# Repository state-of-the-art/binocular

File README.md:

# Binocular

Project aims to design the open hardware binocular wearing computer platform. It's PCB design and
the related software should be open to drive the development of VR/AR glasses for masses.

## Project Goal

To speedup the future come, where AR is a necessary part of the regular reality, like internet now.

## Designs

* [Prototype 1](design/prototype_1)

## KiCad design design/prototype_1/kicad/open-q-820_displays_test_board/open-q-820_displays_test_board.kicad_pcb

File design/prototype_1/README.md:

# Prototype 1

The first prototype with the custom PCB design to fuse the SOM and modules together. Basically it
contains a number of buttons, leds, dual USB-C interface and a way to put SOM in place and connect
the displays.

## Requirements

1. Open Source and Open Hardware platform for light-weight wearable stereo displays as close as
currently possible to the regular glasses
2. No AR-grade positioning detection - just good quality high resolution see-through displays
(1920x1080)
3. Wireless (WiFi ac, h264/h265, battery power) and direct drive (USB-C DP alt-mode)

## Components

* [Platform](../../platform/snapdragon_820/open-q-u820/) - Open-Q µSOM 820
   * SOC - Snapdragon 820
* [Modules](../../modules/enmesi/r6) - Enmesi R6
  Birdbath (the best weight/quality ratio for now)
   * Displays - Sony ECX335S
* [PCB](pcb) - where SOM & Modules are met
* [Frame](frame) - TODO

## Documents

* [Design Document](Design Document.pdf)

## Configuring

In order to make Open-Q µSOM 820 work on the prototype - it should have a specific rpm partition
with modified LDO voltages. For this purpose it's better to get the original rpm partition from the
board, alter it's binary structure to write the required values into the special structure, resign
it and write back to the board.

To do that it's needed to have the original devboard for the prototype test board. Prototype release
will support protection for the used rails and will allow to flash any µSOM to the needed state.

**WARNING**: this is dangerous - writing the low-level partitions and especially altering them could
make your µSOM and devboard not bootable with common methods (only by EDL recovery), and the
operation we're going to do will make the µSOM not to work with devboard until the partition will
be restored. So you know - as is.

### Get with ADB

You can receive the rpm partition with root ADB.

1. Connect your devboard to power source
2. Connect the `USB2.0 (ADB)` to you host computer
3. Boot the devboard to android by pressing `ON/OFF` button
4. When the board boot-up switch the adbd to root mode and get the rpm partition this way:
   ```
   host $ adb root
   restarting adbd as root

   host $ adb shell cat /dev/block/by-name/rpm > rpm.img
   ```
5. And now you have the rpm partition image

### Modify the RPM partition

The voltages in the original RPM configuration is not suitable, so we need to reconfigure them.

1. Modify the `rpm.img` with [rpm_ldo_rail_tool.py](../../platform/snapdragon_820/tools/rpm_ldo_rail_tool.py):
   ```
   host $ platform/snapdragon_820/tools/rpm_ldo_rail_tool.py rpm.img
   Search for magic 00000000000000000a9001: 0x1000 0x2000 0x3000 0x4000 0x5000 0x6000 0x7000 0x8000 0x9000 0xa000 0xb000 0xc000 0xd000 0xe000 0xf000 0x10000 0x11000 0x12000 0x13000 0x14000 0x15000 0x16000 0x17000 0x18000 0x19000 0x1a000 0x1b000 0x1c000 0x1d000 0x1e000 0x1f000 0x20000 0x21000 0x22000 0x23000 0x24000 0x25000 0x26000 0x27000 0x28000 0x29000 0x2a000 0x2b000 0x2c000 0x2d000 0x2e000 0x2f000 0x30000 0x31000 0x32000 0x33000
   LDO struct was found on address 0x33098 processing...

   LDO14 raw: 0ac01202a406ea0b00000300
      Current Threshold: 10mA, Safety Headroom: 300mV
      Voltage Min: 1.700V
      Voltage Max: 3.050V
   LDO15 raw: 0ac012020807080700000300
      Current Threshold: 10mA, Safety Headroom: 300mV
    ! Voltage Min: 1.800V -> 1.200V
    ! Voltage Max: 1.800V -> 1.500V
   LDO17 raw: 0aa00f02c4098c0a00000300
      Current Threshold: 10mA, Safety Headroom: 250mV
    ! Voltage Min: 2.500V -> 1.750V
    ! Voltage Max: 2.700V -> 3.300V
   LDO18 raw: 0a800c028c0a540b00000200
      Current Threshold: 10mA, Safety Headroom: 200mV
    ! Voltage Min: 2.700V -> 1.800V
      Voltage Max: 2.900V
   LDO19 raw: 0a400602220b1c0c00000300
      Current Threshold: 10mA, Safety Headroom: 100mV
    ! Voltage Min: 2.850V -> 1.200V
    ! Voltage Max: 3.100V -> 1.500V
   LDO21 raw: 0ac012028c0a860b00000200
      Current Threshold: 10mA, Safety Headroom: 300mV
    ! Voltage Min: 2.700V -> 1.750V
    ! Voltage Max: 2.950V -> 3.300V
   LDO22 raw: 0ac01202d606e40c00000300
      Current Threshold: 10mA, Safety Headroom: 300mV
      Voltage Min: 1.750V
      Voltage Max: 3.300V
   LDO23 raw: 0a800c028c0a540b00000300
      Current Threshold: 10mA, Safety Headroom: 200mV
    ! Voltage Min: 2.700V -> 1.800V
      Voltage Max: 2.900V
   LDO29 raw: 05900102be0a220b00000300
      Current Threshold: 5mA, Safety Headroom: 25mV
    ! Voltage Min: 2.750V -> 1.750V
    ! Voltage Max: 2.850V -> 3.300V

   Result of modified rpm: rpm_mod.img
   Search complete
   ```
2. When you've get your `rpm_mod.img` - you need to sign it by [qtestsign](https://github.com/msm8916-mainline/qtestsign)
   ```
   host $ git clone https://github.com/msm8916-mainline/qtestsign
   Cloning into 'qtestsign'...
   remote: Enumerating objects: 17, done.
   remote: Counting objects: 100% (17/17), done.
   remote: Compressing objects: 100% (11/11), done.
   remote: Total 17 (delta 3), reused 17 (delta 3), pack-reused 0
   Unpacking objects: 100% (17/17), 16.64 KiB | 97.00 KiB/s, done.

   host $ cd qtestsign

   host $ python3 -m venv .venv

   host $ . .venv/bin/activate

   host $ pip install -r requirements.txt
   Collecting cryptography>=3.1
     Downloading cryptography-36.0.1-cp36-abi3-manylinux_2_17_x86_64.manylinux2014_x86_64.whl (3.8 MB
   )
        |████████████████████████████████| 3.8 MB 321 kB/s
   Collecting cffi>=1.12
     Downloading cffi-1.15.0-cp38-cp38-manylinux_2_12_x86_64.manylinux2010_x86_64.whl (446 kB)
        |████████████████████████████████| 446 kB 41.9 MB/s
   Collecting pycparser
     Downloading pycparser-2.21-py2.py3-none-any.whl (118 kB)
        |████████████████████████████████| 118 kB 35.8 MB/s
   Installing collected packages: pycparser, cffi, cryptography
   Successfully installed cffi-1.15.0 cryptography-36.0.1 pycparser-2.21

   host $ ./qtestsign.py rpm rpm_mod.img
   Before: Elf(ehdr=Ehdr(ei_magic=b'\x7fELF', ei_class=1, ei_data=1, ei_version=1, ei_os_abi=0, ei_abi_version=0, e_type=2, e_machine=40, e_version=1, e_entry=9, e_phoff=52, e_shoff=0, e_flags=83886082, e_ehsize=52, e_phentsize=32, e_phnum=4, e_shentsize=40, e_shnum=0, e_shstrndx=0), phdrs=[Phdr(p_type=0, p_offset=0, p_vaddr=0, p_paddr=0, p_filesz=180, p_memsz=0, p_flags=117440512, p_align=0), Phdr(p_type=0, p_offset=4096, p_vaddr=2752512, p_paddr=2752512, p_filesz=6568, p_memsz=8192, p_flags=35651584, p_align=4096), Phdr(p_type=1, p_offset=12288, p_vaddr=0, p_paddr=2097152, p_filesz=163472, p_memsz=163472, p_flags=2147483655, p_align=4), Phdr(p_type=1, p_offset=175760, p_vaddr=589824, p_paddr=2686976, p_filesz=53692, p_memsz=61884, p_flags=7, p_align=32)])
   Header(version=0, type=3, flash_addr=0, dest_addr=2752552, total_size=2432, hash_size=128, signature_addr=2752680, signature_size=256, cert_chain_addr=2752936, cert_chain_size=2048)
   After: Elf(ehdr=Ehdr(ei_magic=b'\x7fELF', ei_class=1, ei_data=1, ei_version=1, ei_os_abi=0, ei_abi_version=0, e_type=2, e_machine=40, e_version=1, e_entry=9, e_phoff=52, e_shoff=0, e_flags=83886082, e_ehsize=52, e_phentsize=32, e_phnum=4, e_shentsize=40, e_shnum=0, e_shstrndx=0), phdrs=[Phdr(p_type=0, p_offset=0, p_vaddr=0, p_paddr=0, p_filesz=180, p_memsz=0, p_flags=117440512, p_align=0),Phdr(p_type=0, p_offset=4096, p_vaddr=2752512, p_paddr=2752512, p_filesz=2472, p_memsz=4096, p_flags=35651584, p_align=4096), Phdr(p_type=1, p_offset=6568, p_vaddr=0, p_paddr=2097152, p_filesz=163472, p_memsz=163472, p_flags=2147483655, p_align=4), Phdr(p_type=1, p_offset=170048, p_vaddr=589824, p_paddr=2686976, p_filesz=53692, p_memsz=61884, p_flags=7, p_align=32)])
   ```
8. And now you have the modified and signed RPM for the binocular prototype - just need to flash it...

### Write with fastboot mode

Unfortunately fastboot doesn't provide a way to read the partition (fetch operation is not working),
but can help to write it back to the flash. After that you will need to dicsonnect your µSOM and
move it to the prototype board.

**WARNING:** after this operation you will not be able to boot the µSOM on Open-Q devboard until
you will restore the RPM partition to the original one. So make sure you have a backup of the
original rpm.img. The voltage changes should not fry your devboard, but better to not leave it on
the powered Open-Q devboard for a long time (precaution).

1. Disconnect the sensors expansion board (precaution)
2. Connect your devboard to power source
3. Connect the `USB2.0 (ADB)` to you host computer
4. Boot the devboard to fastboot mode by pressing `VOL (-)` and `ON/OFF` buttons together
5. Check the fastboot device connected properly:
   ```
   host $ fastboot devices
   277010101071910397      fastboot
   ```
6. Flash the modified RPM to the board
   ```
   host $ fastboot flash rpm rpm_mod-test-signed.mbn
   Sending 'rpm' (218 KB)                             OKAY [  0.037s]
   Writing 'rpm'                                      OKAY [  0.026s]
   Finished. Total time: 0.115s
   ```

### Using EDL mode

EDL mode is advanced recovery mode for Qualcomm SoC and needs some additional knowledge, but if you
want to dig in (or have no choice because your bootloader is not working well anymore) - welcome to
the special page about it: [EDL Mode](../../platform/snapdragon_820/open-q-u820/edl_mode.md)

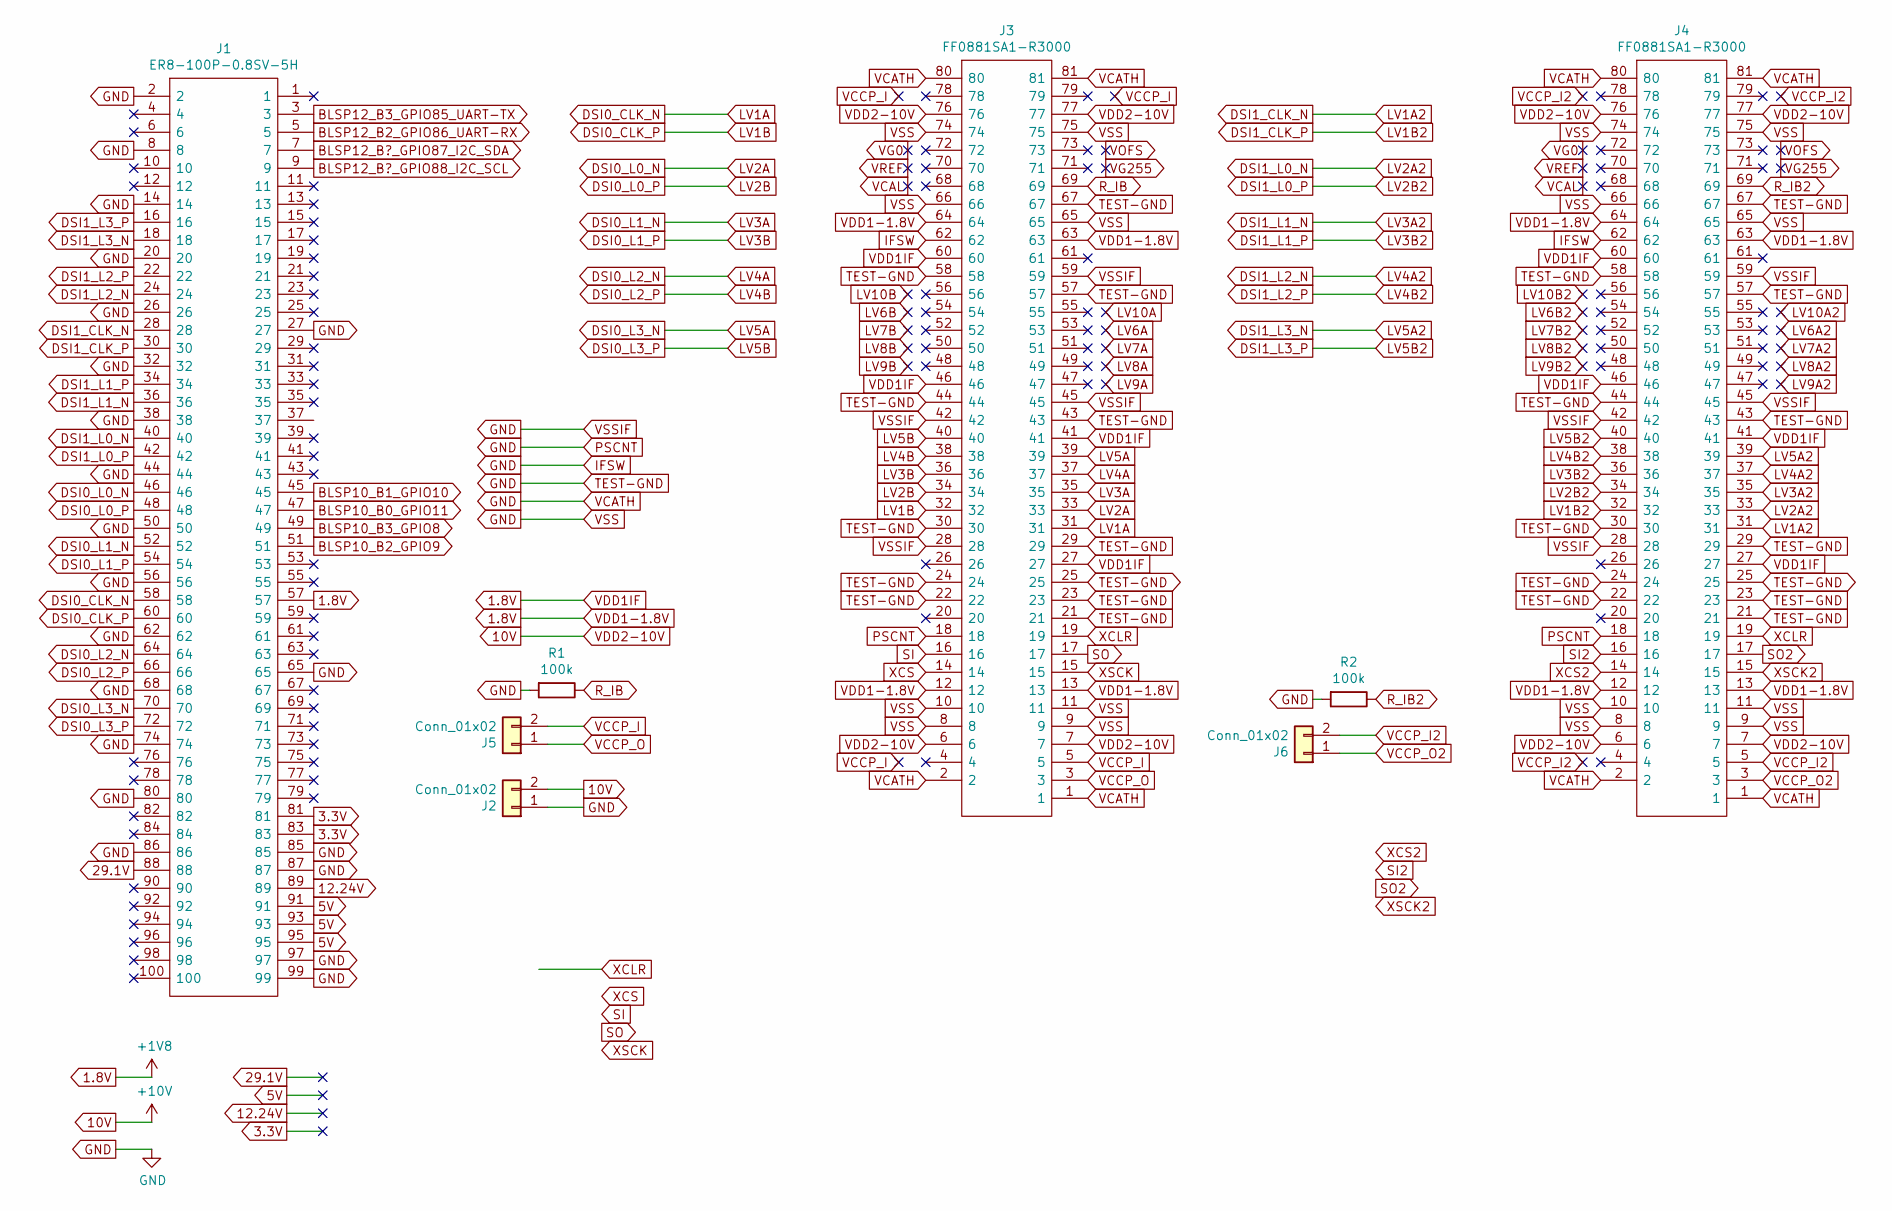
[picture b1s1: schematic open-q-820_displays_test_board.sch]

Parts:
J1: ER8-100P-0.8SV-5H; ER8100P08SV5H; Manufacturer_Part_Number ER8-100P-0.8SV-5H; Mouser Part Number 798-ER8-100P-08SV-5H
J2, J5, J6: Conn_01x02; PinHeader_1x02_P2.54mm_Vertical
J3, J4: FF0881SA1-R3000; FF0881SA1R3000; Manufacturer_Part_Number FF0881SA1-R3000; Mouser Part Number 656-FF0881SA1-R3000
R1, R2: 100k; R_Axial_DIN0204_L3.6mm_D1.6mm_P5.08mm_Horizontal

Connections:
1.8V: J1.57, J3.12, J3.13, J3.27, J3.41, J3.46, J3.60, J3.63, J3.64, J4.12, J4.13, J4.27, J4.41, J4.46, J4.60, J4.63, J4.64
3.3V: J1.81, J1.83
5V: J1.91, J1.93, J1.95
10V: J2.2, J3.6, J3.7, J3.76, J3.77, J4.6, J4.7, J4.76, J4.77
12.24V: J1.89
29.1V: J1.88
DSI0_CLK_N: J1.58, J3.31
DSI0_CLK_P: J1.60, J3.32
DSI0_L0_N: J1.46, J3.33
DSI0_L0_P: J1.48, J3.34
DSI0_L1_N: J1.52, J3.35
DSI0_L1_P: J1.54, J3.36
DSI0_L2_N: J1.64, J3.37
DSI0_L2_P: J1.66, J3.38
DSI0_L3_N: J1.70, J3.39
DSI0_L3_P: J1.72, J3.40
DSI1_CLK_N: J1.28, J4.31
DSI1_CLK_P: J1.30, J4.32
DSI1_L0_N: J1.40, J4.33
DSI1_L0_P: J1.42, J4.34
DSI1_L1_N: J1.36, J4.35
DSI1_L1_P: J1.34, J4.36
DSI1_L2_N: J1.24, J4.37
DSI1_L2_P: J1.22, J4.38
DSI1_L3_N: J1.18, J4.39
DSI1_L3_P: J1.16, J4.40
R_IB: J3.69, R1.1
R_IB2: J4.69, R2.1
VCCP_I: J3.5, J5.2
VCCP_I2: J4.5, J6.2
VCCP_O: J3.3, J5.1
VCCP_O2: J4.3, J6.1

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
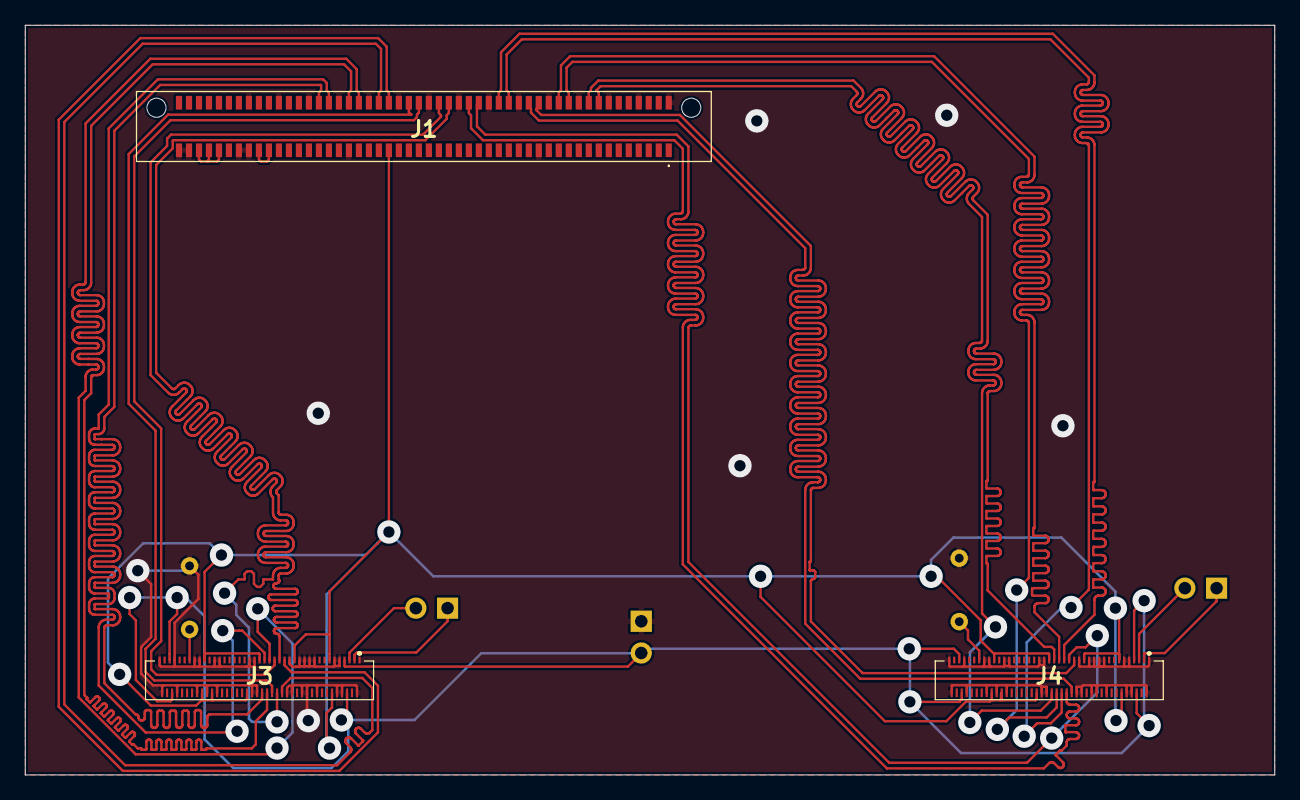
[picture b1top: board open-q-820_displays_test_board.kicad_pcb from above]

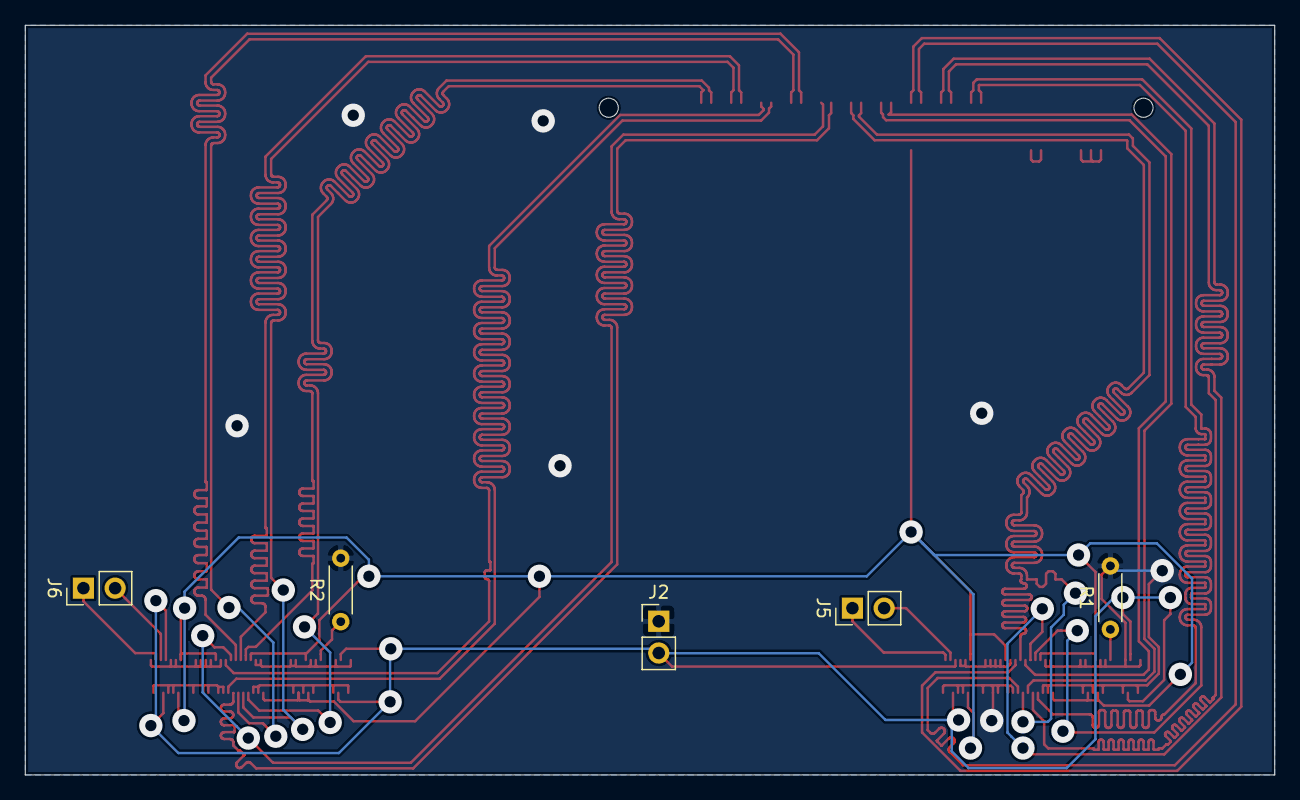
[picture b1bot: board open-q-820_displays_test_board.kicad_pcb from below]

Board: 2 copper layers, 100.0 x 60.0 mm, 8 parts (5 on the bottom side), 31 nets.

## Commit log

2021-03-22 Added Binocular first prototype
2021-03-22 Added display test board incomplete kicad project
2021-03-22 Added ecx335s display document
2021-03-22 Added snapdragon 820 msm8996 documentation
2021-03-22 Added open-q 820 build instructions and captured information
2021-03-22 Added useful docs for open-q 820 board
2021-04-03 Added first edition of the icon
2021-04-03 Second generation of the icon
2021-04-07 Another version of the icon
2021-09-10 Added first kicad export and pdf with eagle schematics
2021-09-29 Added BOM from 20210929 for the first prototype
2021-10-15 Updated BOM
2021-10-15 Added BOM sets number and price
2021-12-27 Added converted Video_1028_1.brd through Altium and updated to KiCAD 6
2022-01-14 Added updated prototype 01 test board
2022-01-14 Updated Design Document to the 2021/05/21 where removed the passthrough req
2022-01-14 Added the original testboard design files
2022-01-14 Removed the display test board due to general failure of the idea
2022-01-14 Moved the kicad schematics and cleaned up a bit
2022-01-14 Added rpm partition modification tool for PM8996 voltages
2022-02-18 Added Qualcomm EDL mode description with and doc how to use edl tool
2022-02-22 Added the steps to flash the required voltages to the board RPM partition
2022-02-22 Added a couple of pictures of connected devboard and in uart mode
2022-02-25 Added the properly working voltages for rpm tool
2022-03-29 Reorganized the RPM modification tool a bit
